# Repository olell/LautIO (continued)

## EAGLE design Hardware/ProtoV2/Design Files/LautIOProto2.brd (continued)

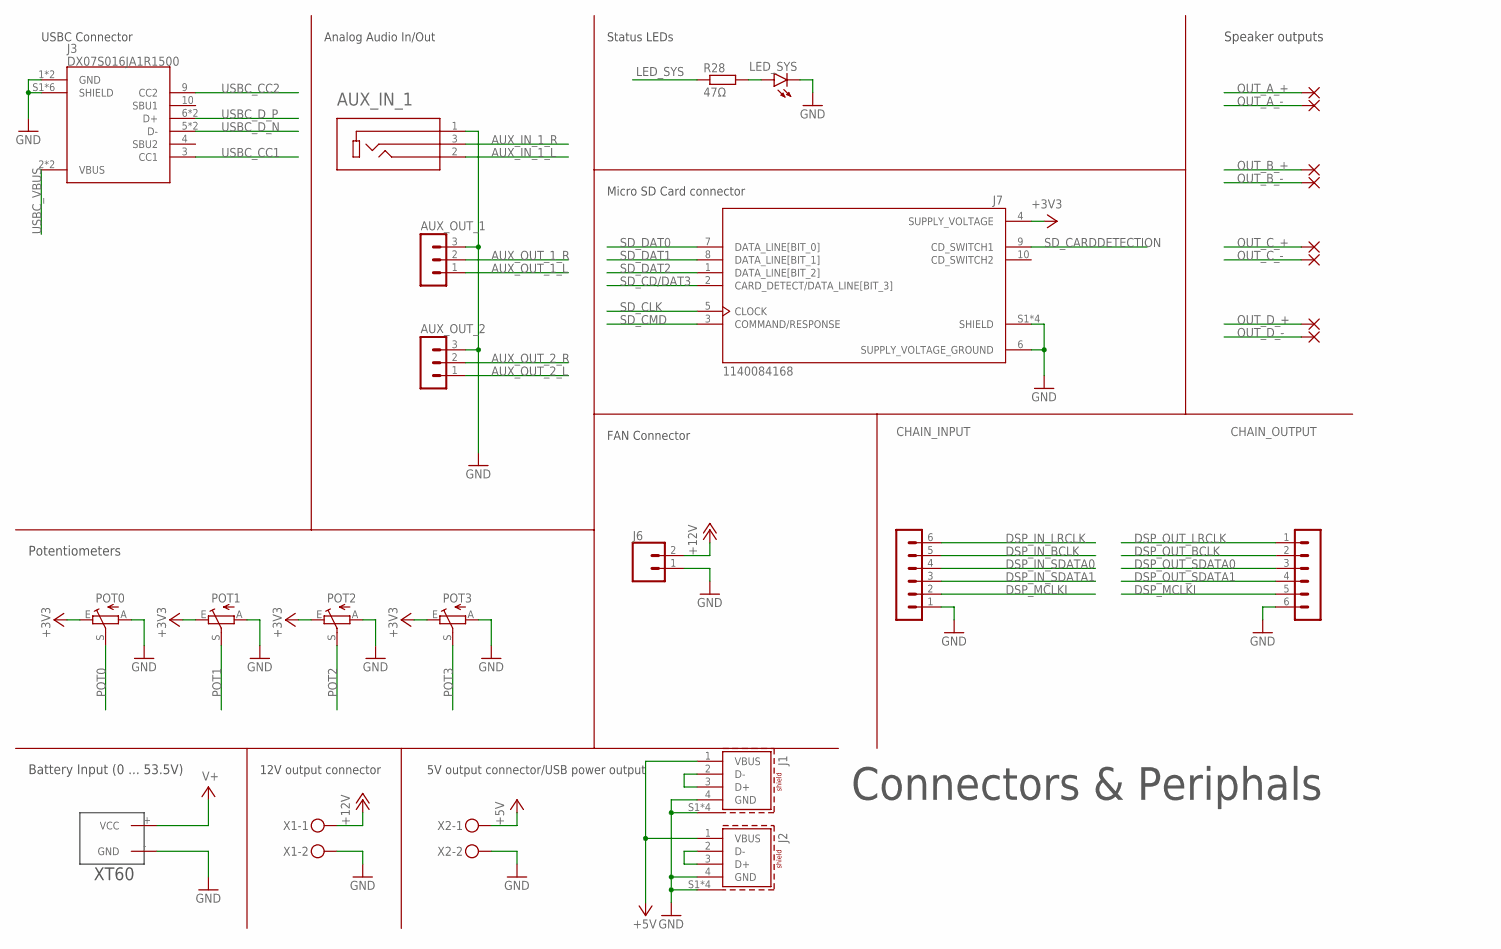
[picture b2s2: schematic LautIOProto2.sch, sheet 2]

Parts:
AUX_IN_1: SJ1-3523N; CUI_SJ1-3523N
AUX_OUT_1, AUX_OUT_2: MA03-1
CHAIN_INPUT: MA06-1
CHAIN_OUTPUT: MA06-1
J1, J2: 614004134726
J3: DX07S016JA1R1500; JAE_DX07S016JA1R1500
J6: CONN_02PTH3; 1X02_LONGPADS
J7: 1140084168; AMPHENOL_1140084168
LED_SYS: LEDSML0603; SML0603
PAD1, PAD2, PAD3, PAD4, PAD5, PAD6, PAD7, PAD8: SMD2; SMD1,27-2,54
POT0, POT1, POT2, POT3: TRIM_EU-CIP20C-6MM; CIP20C-6MM
R28: 47Ω; R0603
U$1: XT60
X1, X2: MKDSN1,5/2-5,08

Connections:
+3V3: J7.4 (SUPPLY_VOLTAGE), POT0.E, POT1.E, POT2.E, POT3.E; also elsewhere on the board
+5V: J1.1 (VBUS), J2.1 (VBUS), X2.1; also elsewhere on the board
+12V: J6.2, X1.1; also elsewhere on the board
AUX_IN_1_L: AUX_IN_1.2; also elsewhere on the board
AUX_IN_1_R: AUX_IN_1.3; also elsewhere on the board
AUX_OUT_1_L: AUX_OUT_1.1; also elsewhere on the board
AUX_OUT_1_R: AUX_OUT_1.2; also elsewhere on the board
AUX_OUT_2_L: AUX_OUT_2.1; also elsewhere on the board
AUX_OUT_2_R: AUX_OUT_2.2; also elsewhere on the board
DSP_IN_BCLK: CHAIN_INPUT.5; also elsewhere on the board
DSP_IN_LRCLK: CHAIN_INPUT.6; also elsewhere on the board
DSP_IN_SDATA0: CHAIN_INPUT.4; also elsewhere on the board
DSP_IN_SDATA1: CHAIN_INPUT.3; also elsewhere on the board
DSP_MCLKI: CHAIN_INPUT.2, CHAIN_OUTPUT.5; also elsewhere on the board
DSP_OUT_BCLK: CHAIN_OUTPUT.2; also elsewhere on the board
DSP_OUT_LRCLK: CHAIN_OUTPUT.1; also elsewhere on the board
DSP_OUT_SDATA0: CHAIN_OUTPUT.3; also elsewhere on the board
DSP_OUT_SDATA1: CHAIN_OUTPUT.4; also elsewhere on the board
GND: AUX_IN_1.1, AUX_OUT_1.3, AUX_OUT_2.3, CHAIN_INPUT.1, CHAIN_OUTPUT.6, J1.4 (GND), J1.S1 (SHIELD), J1.S2 (SHIELD), J1.S3 (SHIELD), J1.S4 (SHIELD), J2.4 (GND), J2.S1 (SHIELD), J2.S2 (SHIELD), J2.S3 (SHIELD), J2.S4 (SHIELD), J3.1 (GND), J3.12 (GND), J3.S1 (SHIELD), J3.S2 (SHIELD), J3.S3 (SHIELD), J3.S4 (SHIELD), J3.S5 (SHIELD), J3.S6 (SHIELD), J6.1, J7.6 (SUPPLY_VOLTAGE_GROUND), J7.S1 (SHIELD), J7.S2 (SHIELD), J7.S3 (SHIELD), J7.S4 (SHIELD), LED_SYS.C, POT0.A, POT1.A, POT2.A, POT3.A, U$1.- (GND), X1.2, X2.2; also elsewhere on the board
LED_SYS: R28.1; also elsewhere on the board
unnamed: J2.2 (D-), J2.3 (D+)
unnamed: J1.2 (D-), J1.3 (D+)
unnamed: LED_SYS.A, R28.2
OUT_A_+: PAD1.1; also elsewhere on the board
OUT_A_-: PAD2.1; also elsewhere on the board
OUT_B_+: PAD4.1; also elsewhere on the board
OUT_B_-: PAD3.1; also elsewhere on the board
OUT_C_+: PAD5.1; also elsewhere on the board
OUT_C_-: PAD6.1; also elsewhere on the board
OUT_D_+: PAD8.1; also elsewhere on the board
OUT_D_-: PAD7.1; also elsewhere on the board
POT0: POT0.S; also elsewhere on the board
POT1: POT1.S; also elsewhere on the board
POT2: POT2.S; also elsewhere on the board
POT3: POT3.S; also elsewhere on the board
SD_CARDDETECTION: J7.9 (CD_SWITCH1); also elsewhere on the board
SD_CD/DAT3: J7.2 (CARD_DETECT/DATA_LINE[BIT_3]); also elsewhere on the board
SD_CLK: J7.5 (CLOCK); also elsewhere on the board
SD_CMD: J7.3 (COMMAND/RESPONSE); also elsewhere on the board
SD_DAT0: J7.7 (DATA_LINE[BIT_0]); also elsewhere on the board
SD_DAT1: J7.8 (DATA_LINE[BIT_1]); also elsewhere on the board
SD_DAT2: J7.1 (DATA_LINE[BIT_2]); also elsewhere on the board
USBC_CC1: J3.3 (CC1); also elsewhere on the board
USBC_CC2: J3.9 (CC2); also elsewhere on the board
USBC_D_N: J3.5 (D-), J3.8 (D-); also elsewhere on the board
USBC_D_P: J3.6 (D+), J3.7 (D+); also elsewhere on the board
USBC_VBUS: J3.2 (VBUS), J3.11 (VBUS); also elsewhere on the board
V+: U$1.+ (VCC); also elsewhere on the board

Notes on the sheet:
Battery Input (0 ... 53.5V)
12V output connector
Connectors & Periphals
5V output connector/USB power output
Potentiometers
Speaker outputs
USBC Connector
Micro SD Card connector
Analog Audio In/Out
Status LEDs
FAN Connector

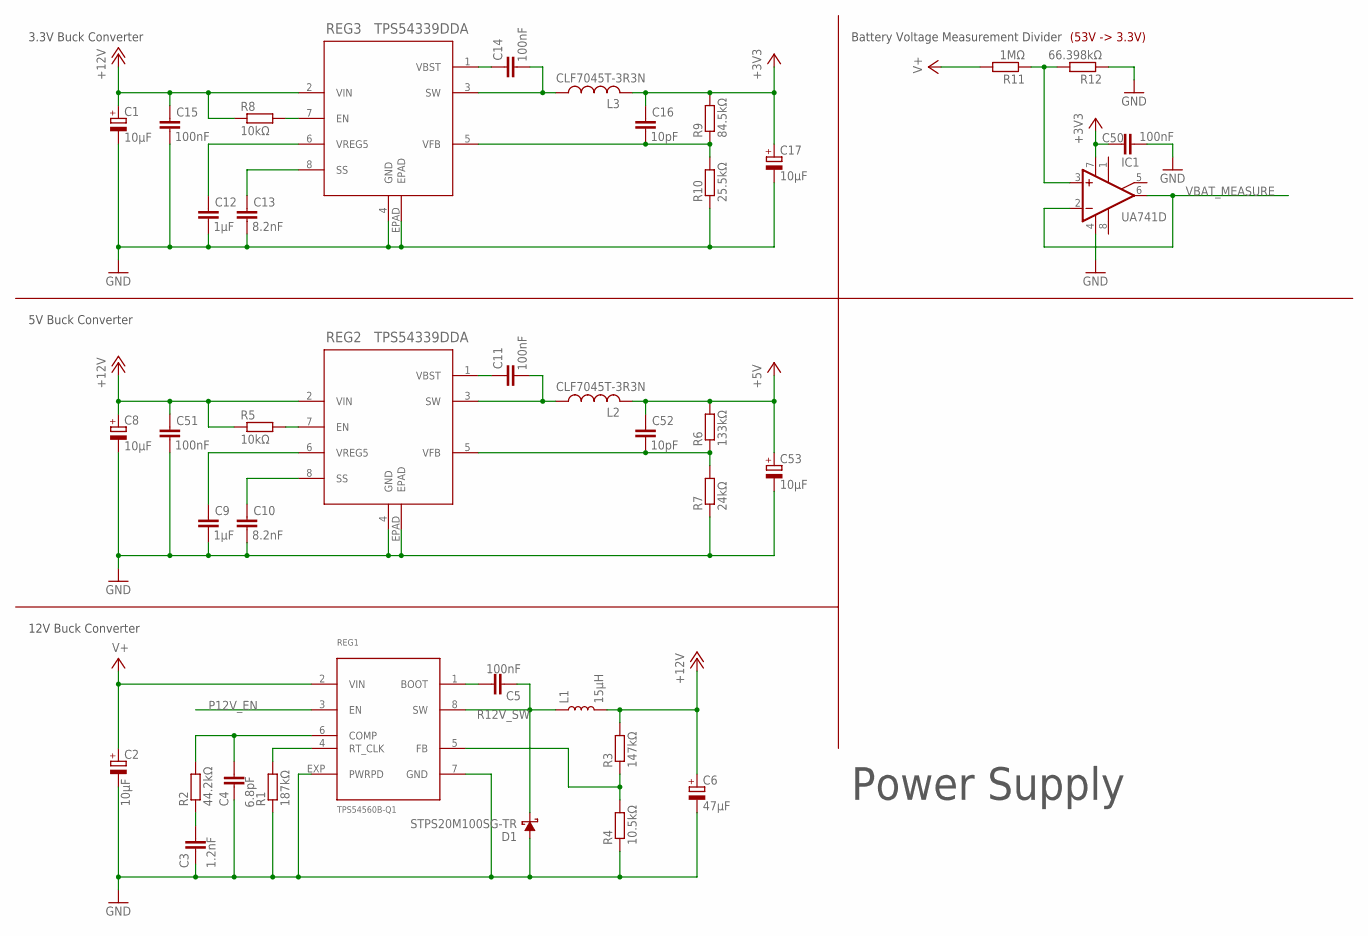
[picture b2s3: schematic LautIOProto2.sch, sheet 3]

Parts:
C1, C2, C8, C17, C53: 10µF; 153CLV-0605
C3: 1.2nF; C0603
C4: 6.8pF; C0603
C5, C11, C14, C15, C50, C51: 100nF; C0603
C6: 47µF; 153CLV-0807
C9, C12: 1µF; C3216
C10, C13: 8.2nF; C0603
C16, C52: 10pF; C0603
D1: STPS20M100SG-TR; TO-263/D2PAK
IC1: UA741D; SO08
L1: 15µH; INDUCTOR_SDR1307
L2, L3: CLF7045T-3R3N; L5650M
R1: 187kΩ; R0603
R2: 44.2kΩ; R0603
R3: 147kΩ; R0603
R4: 10.5kΩ; R0603
R5, R8: 10kΩ; R0603
R6: 133kΩ; R0603
R7: 24kΩ; R0603
R9: 84.5kΩ; R0603
R10: 25.5kΩ; R0603
R11: 1MΩ; R0603
R12: 66.398kΩ; R0603
REG1: TPS54560B-Q1; HSOP8
REG2, REG3: TPS54339DDA; DDA8_3P1X2P4_TEX

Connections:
+3V3: C16.1, C17.+, C50.1, IC1.7 (V+), L3.2, R9.2; also elsewhere on the board
+5V: C52.1, C53.+, L2.2, R6.2; also elsewhere on the board
+12V: C1.+, C6.+, C8.+, C15.1, C51.1, L1.P$2 (2), R3.2, R5.1, R8.1, REG2.2 (VIN), REG3.2 (VIN); also elsewhere on the board
GND: C1.-, C2.-, C3.2, C4.2, C6.-, C8.-, C9.2, C10.2, C12.2, C13.2, C15.2, C17.-, C50.2, C51.2, C53.-, D1.1 (A), D1.3 (A), IC1.4 (V-), R1.1, R4.1, R7.1, R10.1, R12.1, REG1.7 (GND), REG1.EXP (PWRPD), REG2.4 (GND), REG2.EPAD, REG3.4 (GND), REG3.EPAD; also elsewhere on the board
unnamed: R1.2, REG1.4 (RT_CLK)
unnamed: C4.1, R2.2, REG1.6 (COMP)
unnamed: C3.1, R2.1
unnamed: C5.1, REG1.1 (BOOT)
unnamed: R3.1, R4.2, REG1.5 (FB)
unnamed: R5.2, REG2.7 (EN)
unnamed: C10.1, REG2.8 (SS)
unnamed: C9.1, REG2.6 (VREG5)
unnamed: C11.1, REG2.1 (VBST)
unnamed: R8.2, REG3.7 (EN)
unnamed: C14.1, REG3.1 (VBST)
unnamed: C13.1, REG3.8 (SS)
unnamed: C12.1, REG3.6 (VREG5)
unnamed: C14.2, L3.1, REG3.3 (SW)
unnamed: C16.2, R9.1, R10.2, REG3.5 (VFB)
unnamed: IC1.3 (+IN), R11.1, R12.2
unnamed: C11.2, L2.1, REG2.3 (SW)
unnamed: C52.2, R6.1, R7.2, REG2.5 (VFB)
P12V_EN: REG1.3 (EN)
R12V_SW: C5.2, D1.2 (C), L1.P$1 (1), REG1.8 (SW)
V+: C2.+, R11.2, REG1.2 (VIN); also elsewhere on the board
VBAT_MEASURE: IC1.2 (-IN), IC1.6 (OUT); also elsewhere on the board

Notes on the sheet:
Power Supply
12V Buck Converter
5V Buck Converter
3.3V Buck Converter
Battery Voltage Measurement Divider
(53V -> 3.3V)

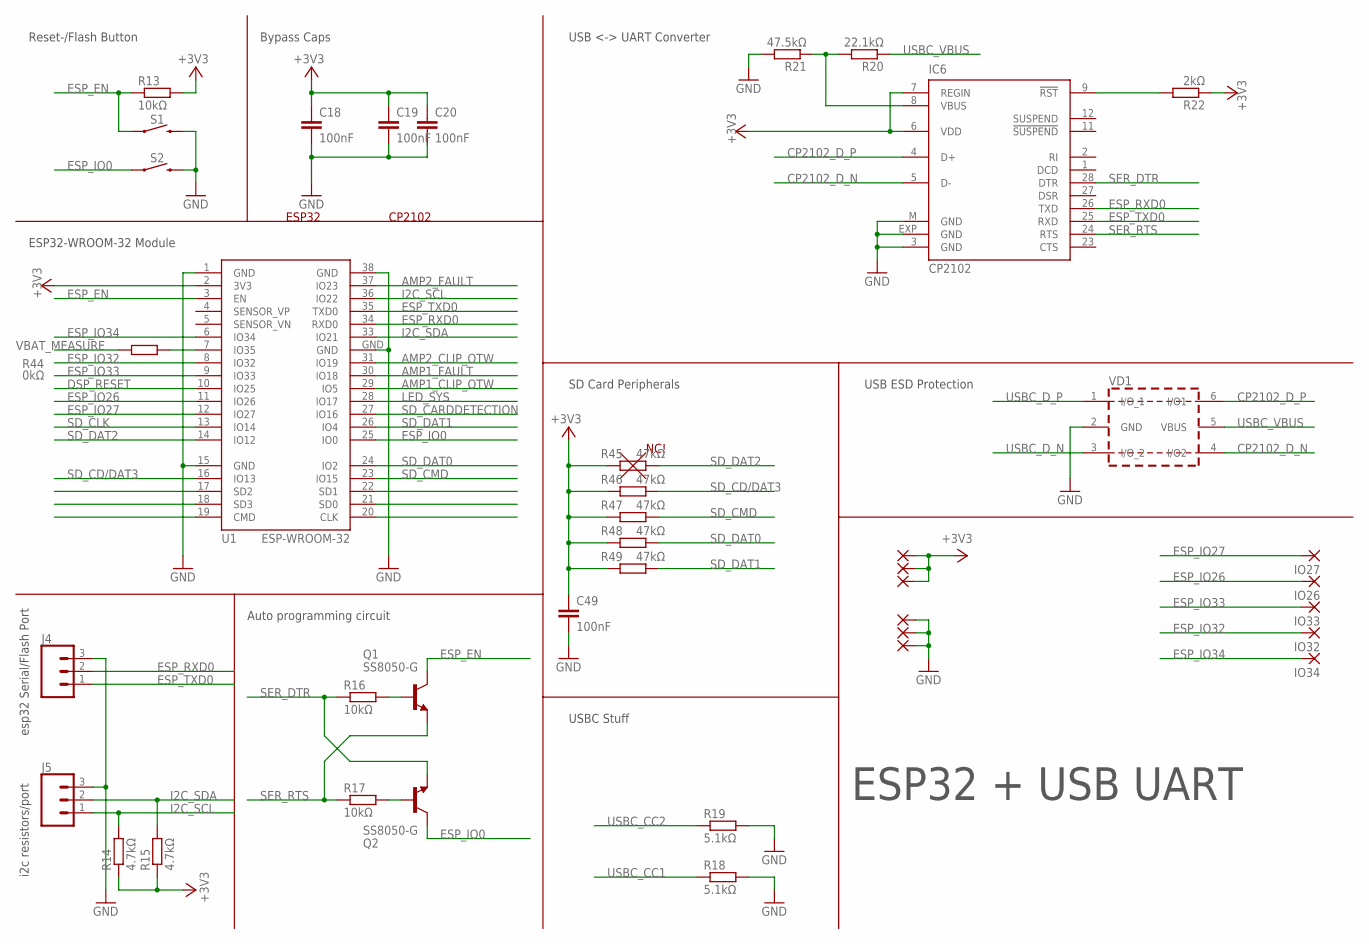
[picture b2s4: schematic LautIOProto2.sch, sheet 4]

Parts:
3V3IO: SMD2; SMD1,27-2,54
C18, C19, C20, C49: 100nF; C0603
IC6: CP2102; MLP28
IO1, IO2, IO3, IO4, IO5, IO26, IO27, IO32, IO33, IO34: SMD2; SMD1,27-2,54
J4, J5: 455-1750-1-ND; 1X03
Q1, Q2: SS8050-G; SOT23-BEC
R13, R16, R17: 10kΩ; R0603
R14, R15: 4.7kΩ; R0603
R18, R19: 5.1kΩ; R0603
R20: 22.1kΩ; R0603
R21: 47.5kΩ; R0603
R22: 2kΩ; R0603
R44: 0kΩ; R0603
R45, R46, R47, R48, R49: 47kΩ; R0603
S1, S2: MOMENTARY-SWITCH-SPST-SMD-6.2MM-TALL; TACTILE_SWITCH_SMD_6.2MM_TALL
U1: ESP-WROOM-32
VD1: USBLC6-2SC6; SOT-23-6L

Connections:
+3V3: 3V3IO.1, C18.1, C19.1, C20.1, C49.1, IC6.6 (VDD), IC6.7 (REGIN), IO2.1, IO3.1, R13.2, R14.1, R15.1, R22.1, R45.1, R46.1, R47.1, R48.1, R49.1, U1.2 (3V3); also elsewhere on the board
AMP1_CLIP_OTW: U1.29 (IO5); also elsewhere on the board
AMP1_FAULT: U1.30 (IO18); also elsewhere on the board
AMP2_CLIP_OTW: U1.31 (IO19); also elsewhere on the board
AMP2_FAULT: U1.37 (IO23); also elsewhere on the board
CP2102_D_N: IC6.5 (D-), VD1.4 (I/O2)
CP2102_D_P: IC6.4 (D+), VD1.6 (I/O1)
DSP_RESET: U1.10 (IO25); also elsewhere on the board
ESP_EN: Q1.C, R13.1, S1.A2 (1), U1.3 (EN)
ESP_IO0: Q2.C, S2.A2 (1), U1.25 (IO0)
ESP_IO26: IO26.1, U1.11 (IO26)
ESP_IO27: IO27.1, U1.12 (IO27)
ESP_IO32: IO32.1, U1.8 (IO32)
ESP_IO33: IO33.1, U1.9 (IO33)
ESP_IO34: IO34.1, U1.6 (IO34)
ESP_RXD0: IC6.26 (TXD), J4.2, U1.34 (RXD0)
ESP_TXD0: IC6.25 (RXD), J4.1, U1.35 (TXD0)
GND: C18.2, C19.2, C20.2, C49.2, IC6.3 (GND), IC6.EXP (GND), IC6.M (GND), IO1.1, IO4.1, IO5.1, J4.3, J5.3, R18.2, R19.2, R21.2, S1.B2 (2), S2.B2 (2), U1.1 (GND), U1.15 (GND), U1.38 (GND), U1.GND, VD1.2 (GND); also elsewhere on the board
I2C_SCL: J5.1, R14.2, U1.36 (IO22); also elsewhere on the board
I2C_SDA: J5.2, R15.2, U1.33 (IO21); also elsewhere on the board
LED_SYS: U1.28 (IO17); also elsewhere on the board
unnamed: Q1.B, R16.2
unnamed: R44.2, U1.7 (IO35)
unnamed: Q2.B, R17.2
unnamed: IC6.8 (VBUS), R20.2, R21.1
unnamed: IC6.9 (!RST), R22.2
SD_CARDDETECTION: U1.27 (IO16); also elsewhere on the board
SD_CD/DAT3: R46.2, U1.16 (IO13); also elsewhere on the board
SD_CLK: U1.13 (IO14); also elsewhere on the board
SD_CMD: R47.2, U1.23 (IO15); also elsewhere on the board
SD_DAT0: R48.2, U1.24 (IO2); also elsewhere on the board
SD_DAT1: R49.2, U1.26 (IO4); also elsewhere on the board
SD_DAT2: R45.2, U1.14 (IO12); also elsewhere on the board
SER_DTR: IC6.28 (DTR), Q2.E, R16.1
SER_RTS: IC6.24 (RTS), Q1.E, R17.1
USBC_CC1: R18.1; also elsewhere on the board
USBC_CC2: R19.1; also elsewhere on the board
USBC_D_N: VD1.3 (I/O_2); also elsewhere on the board
USBC_D_P: VD1.1 (I/O_1); also elsewhere on the board
USBC_VBUS: R20.1, VD1.5 (VBUS); also elsewhere on the board
VBAT_MEASURE: R44.1; also elsewhere on the board

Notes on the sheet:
ESP32 + USB UART
Reset-/Flash Button
Bypass Caps
ESP32-WROOM-32 Module
esp32 Serial/Flash Port
i2c resistors/port
Auto programming circuit
USBC Stuff
ESP32
CP2102
USB <-> UART Converter
USB ESD Protection
NC!
SD Card Peripherals

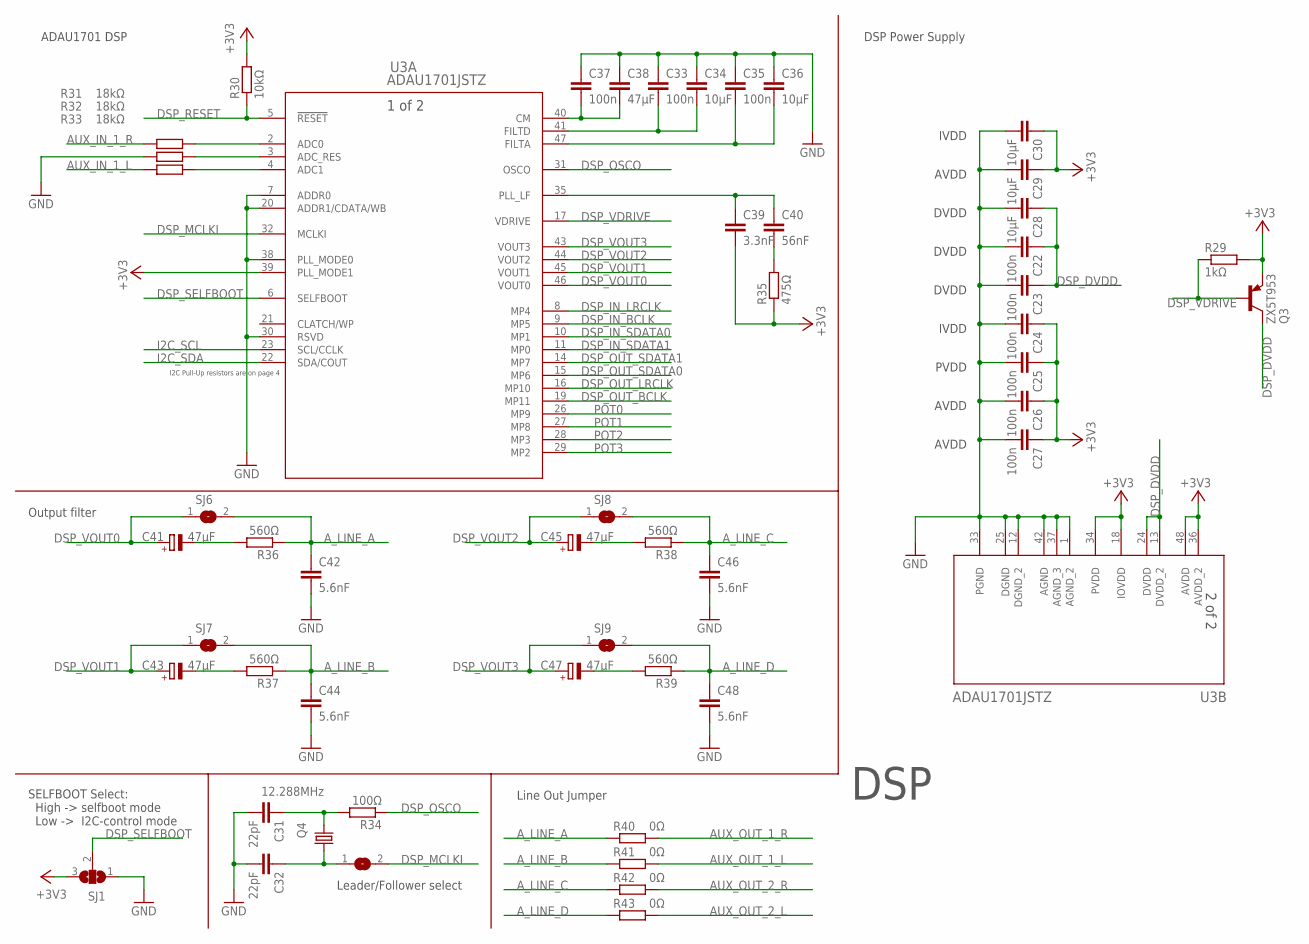
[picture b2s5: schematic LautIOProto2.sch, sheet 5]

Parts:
C22, C23, C24, C25, C26, C27, C33, C35, C37: 100n; C0603
C28, C29, C30, C34, C36: 10µF; C1206K
C31, C32: 22pF; C0603
C38: 47µF; C1206K
C39: 3.3nF; C0603
C40: 56nF; C0603
C41, C43, C45, C47: 47µF; 153CLV-0605
C42, C44, C46, C48: 5.6nF; C0603
Q3: ZX5T953; SOT223
Q4: 12.288MHz; CSM-7X-DU
R29: 1kΩ; R0603
R30: 10kΩ; R0603
R31, R32, R33: 18kΩ; R0603
R34: 100Ω; R0603
R35: 475Ω; R0603
R36, R37, R38, R39: 560Ω; R0603
R40, R41, R42, R43: 0Ω; R0603
SJ1: SJ2W; SJ_2
SJ2, SJ6, SJ7, SJ8, SJ9: SJ
U3: ADAU1701JSTZ; ST_48_ADI

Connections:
+3V3: C24.1, C25.1, C26.1, C27.1, C29.1, C30.1, C39.2, Q3.3 (E), R29.2, R30.2, R35.1, SJ1.3, U3.18 (IOVDD), U3.34 (PVDD), U3.36 (AVDD_2), U3.39 (PLL_MODE1), U3.48 (AVDD); also elsewhere on the board
AUX_IN_1_L: R33.2; also elsewhere on the board
AUX_IN_1_R: R31.2; also elsewhere on the board
AUX_OUT_1_L: R41.2; also elsewhere on the board
AUX_OUT_1_R: R40.2; also elsewhere on the board
AUX_OUT_2_L: R43.2; also elsewhere on the board
AUX_OUT_2_R: R42.2; also elsewhere on the board
A_LINE_A: C42.1, R36.1, R40.1, SJ6.2; also elsewhere on the board
A_LINE_B: C44.1, R37.1, R41.1, SJ7.2; also elsewhere on the board
A_LINE_C: C46.1, R38.1, R42.1, SJ8.2; also elsewhere on the board
A_LINE_D: C48.1, R39.1, R43.1, SJ9.2; also elsewhere on the board
CRYSTAL_MCLKI: C32.1, Q4.1, SJ2.1
DSP_DVDD: C22.1, C23.1, C28.1, Q3.2 (C), Q3.4 (C), U3.13 (DVDD_2), U3.24 (DVDD)
DSP_IN_BCLK: U3.9 (MP5); also elsewhere on the board
DSP_IN_LRCLK: U3.8 (MP4); also elsewhere on the board
DSP_IN_SDATA0: U3.10 (MP1); also elsewhere on the board
DSP_IN_SDATA1: U3.11 (MP0); also elsewhere on the board
DSP_MCLKI: SJ2.2, U3.32 (MCLKI); also elsewhere on the board
DSP_OSCO: R34.1, U3.31 (OSCO)
DSP_OUT_BCLK: U3.19 (MP11); also elsewhere on the board
DSP_OUT_LRCLK: U3.16 (MP10); also elsewhere on the board
DSP_OUT_SDATA0: U3.15 (MP6); also elsewhere on the board
DSP_OUT_SDATA1: U3.14 (MP7); also elsewhere on the board
DSP_RESET: R30.1, U3.5 (!RESET); also elsewhere on the board
DSP_SELFBOOT: SJ1.2, U3.6 (SELFBOOT)
DSP_VDRIVE: Q3.1 (B), R29.1, U3.17 (VDRIVE)
DSP_VOUT0: C41.+, SJ6.1, U3.46 (VOUT0)
DSP_VOUT1: C43.+, SJ7.1, U3.45 (VOUT1)
DSP_VOUT2: C45.+, SJ8.1, U3.44 (VOUT2)
DSP_VOUT3: C47.+, SJ9.1, U3.43 (VOUT3)
GND: C22.2, C23.2, C24.2, C25.2, C26.2, C27.2, C28.2, C29.2, C30.2, C31.2, C32.2, C33.1, C34.1, C35.1, C36.1, C37.1, C38.1, C42.2, C44.2, C46.2, C48.2, R32.2, SJ1.1, U3.1 (AGND_2), U3.7 (ADDR0), U3.12 (DGND_2), U3.20 (ADDR1/CDATA/WB), U3.25 (DGND), U3.30 (RSVD), U3.33 (PGND), U3.37 (AGND_3), U3.38 (PLL_MODE0), U3.42 (AGND); also elsewhere on the board
I2C_SCL: U3.23 (SCL/CCLK); also elsewhere on the board
I2C_SDA: U3.22 (SDA/COUT); also elsewhere on the board
unnamed: R31.1, U3.2 (ADC0)
unnamed: R32.1, U3.3 (ADC_RES)
unnamed: R33.1, U3.4 (ADC1)
unnamed: C31.1, Q4.2, R34.2
unnamed: C33.2, C34.2, U3.41 (FILTD)
unnamed: C35.2, C36.2, U3.47 (FILTA)
unnamed: C37.2, C38.2, U3.40 (CM)
unnamed: C39.1, C40.1, U3.35 (PLL_LF)
unnamed: C40.2, R35.2
unnamed: C41.-, R36.2
unnamed: C43.-, R37.2
unnamed: C45.-, R38.2
unnamed: C47.-, R39.2
POT0: U3.26 (MP9); also elsewhere on the board
POT1: U3.27 (MP8); also elsewhere on the board
POT2: U3.28 (MP3); also elsewhere on the board
POT3: U3.29 (MP2); also elsewhere on the board

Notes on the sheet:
DSP
DSP Power Supply
AVDD
PVDD
IVDD
DVDD
I2C Pull-Up resistors are on page 4
SELFBOOT Select: High -> selfboot mode Low -> I2C-control mode
Output filter
Line Out Jumper
ADAU1701 DSP
Leader/Follower select

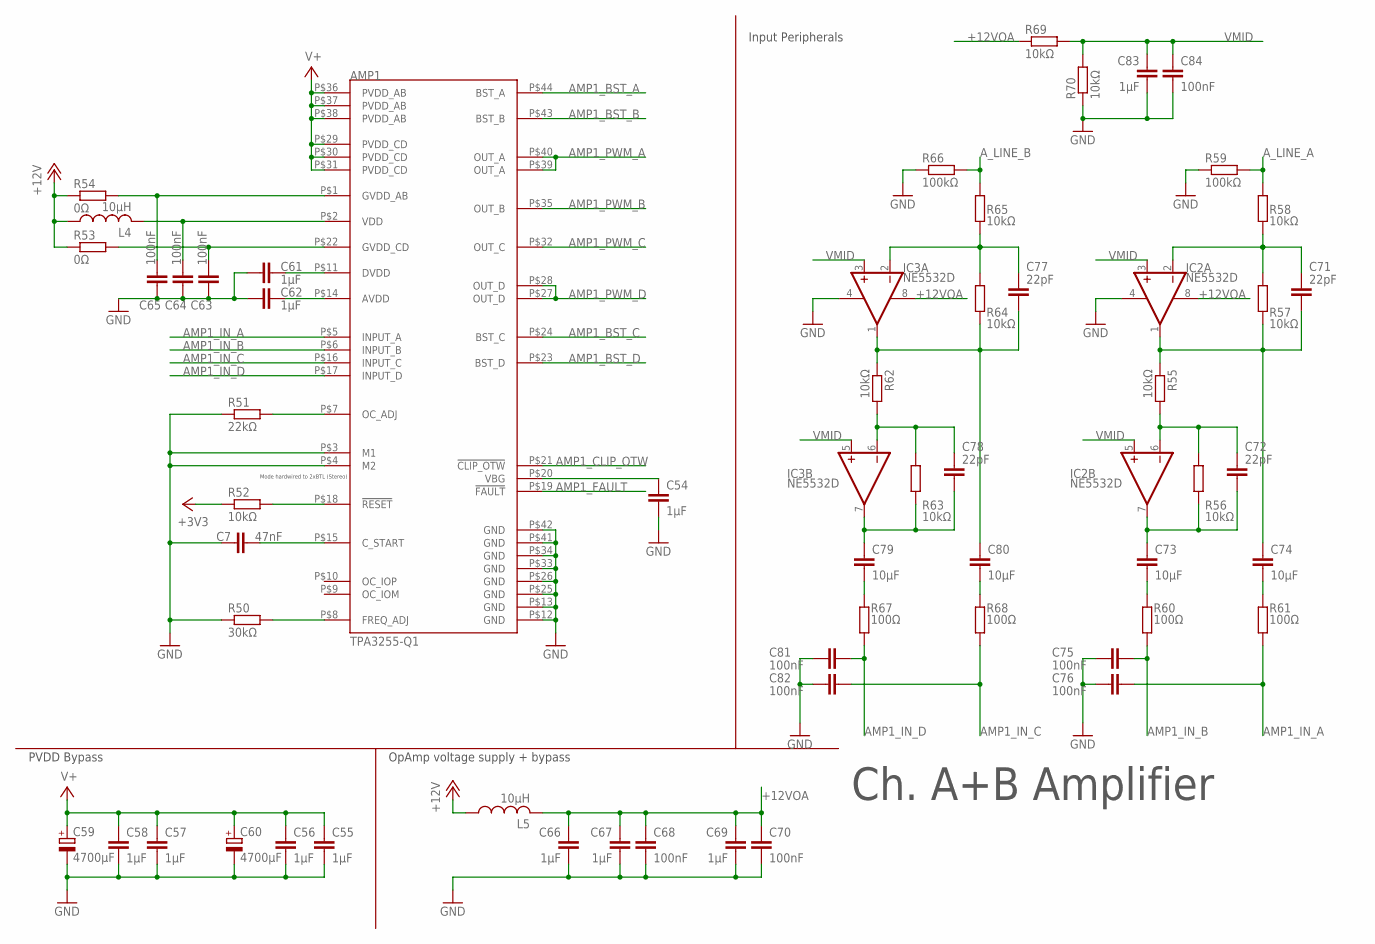
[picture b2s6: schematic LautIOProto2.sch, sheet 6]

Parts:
AMP1: TPA3255-Q1; HTSSOP44
C7: 47nF; C0603
C54, C55, C56, C57, C58, C61, C62, C66, C67, C69, C83: 1µF; C3216
C59, C60: 4700µF; EB22,5D
C63, C64, C65, C68, C70, C75, C76, C81, C82, C84: 100nF; C0603
C71, C72, C77, C78: 22pF; C0603
C73, C74, C79, C80: 10µF; C3216
IC2, IC3: NE5532D; SO08
L4, L5: 10µH; L2012C
R50: 30kΩ; R0603
R51: 22kΩ; R0603
R52, R55, R56, R57, R58, R62, R63, R64, R65, R69, R70: 10kΩ; R0603
R53, R54: 0Ω; R0603
R59, R66: 100kΩ; R0603
R60, R61, R67, R68: 100Ω; R0603

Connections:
+3V3: R52.1; also elsewhere on the board
+12V: L4.1, L5.1, R53.1, R54.1; also elsewhere on the board
+12VOA: C66.1, C67.1, C68.1, C69.1, C70.1, IC2.8 (V+), IC3.8 (V+), L5.2, R69.1
AMP1_BST_A: AMP1.P$44 (BST_A); also elsewhere on the board
AMP1_BST_B: AMP1.P$43 (BST_B); also elsewhere on the board
AMP1_BST_C: AMP1.P$24 (BST_C); also elsewhere on the board
AMP1_BST_D: AMP1.P$23 (BST_D); also elsewhere on the board
AMP1_CLIP_OTW: AMP1.P$21 (!CLIP_OTW); also elsewhere on the board
AMP1_FAULT: AMP1.P$19 (!FAULT); also elsewhere on the board
AMP1_IN_A: AMP1.P$5 (INPUT_A), C76.2, R61.2
AMP1_IN_B: AMP1.P$6 (INPUT_B), C75.2, R60.2
AMP1_IN_C: AMP1.P$16 (INPUT_C), C82.2, R68.2
AMP1_IN_D: AMP1.P$17 (INPUT_D), C81.2, R67.2
AMP1_PWM_A: AMP1.P$39 (OUT_A), AMP1.P$40 (OUT_A); also elsewhere on the board
AMP1_PWM_B: AMP1.P$35 (OUT_B); also elsewhere on the board
AMP1_PWM_C: AMP1.P$32 (OUT_C); also elsewhere on the board
AMP1_PWM_D: AMP1.P$27 (OUT_D), AMP1.P$28 (OUT_D); also elsewhere on the board
A_LINE_A: R58.1, R59.2; also elsewhere on the board
A_LINE_B: R65.1, R66.2; also elsewhere on the board
GND: AMP1.P$3 (M1), AMP1.P$4 (M2), AMP1.P$12 (GND), AMP1.P$13 (GND), AMP1.P$25 (GND), AMP1.P$26 (GND), AMP1.P$33 (GND), AMP1.P$34 (GND), AMP1.P$41 (GND), AMP1.P$42 (GND), C7.1, C54.2, C55.2, C56.2, C57.2, C58.2, C59.-, C60.-, C61.2, C62.2, C63.2, C64.2, C65.2, C66.2, C67.2, C68.2, C69.2, C70.2, C75.1, C76.1, C81.1, C82.1, C83.2, C84.2, IC2.4 (V-), IC3.4 (V-), R50.1, R51.1, R59.1, R66.1, R70.1; also elsewhere on the board
unnamed: AMP1.P$15 (C_START), C7.2
unnamed: AMP1.P$8 (FREQ_ADJ), R50.2
unnamed: AMP1.P$7 (OC_ADJ), R51.2
unnamed: AMP1.P$18 (!RESET), R52.2
unnamed: AMP1.P$20 (VBG), C54.1
unnamed: AMP1.P$11 (DVDD), C61.1
unnamed: AMP1.P$14 (AVDD), C62.1
unnamed: AMP1.P$1 (GVDD_AB), C65.1, R54.2
unnamed: AMP1.P$2 (VDD), C64.1, L4.2
unnamed: AMP1.P$22 (GVDD_CD), C63.1, R53.2
unnamed: C71.1, IC2.2 (-IN), R57.1, R58.2
unnamed: C71.2, C74.1, IC2.1 (OUT), R55.1, R57.2
unnamed: C72.1, IC2.6 (-IN), R55.2, R56.1
unnamed: C77.1, IC3.2 (-IN), R64.1, R65.2
unnamed: C72.2, C73.1, IC2.7 (OUT), R56.2
unnamed: C77.2, C80.1, IC3.1 (OUT), R62.1, R64.2
unnamed: C78.1, IC3.6 (-IN), R62.2, R63.1
unnamed: C74.2, R61.1
unnamed: C73.2, R60.1
unnamed: C78.2, C79.1, IC3.7 (OUT), R63.2
unnamed: C80.2, R68.1
unnamed: C79.2, R67.1
V+: AMP1.P$29 (PVDD_CD), AMP1.P$30 (PVDD_CD), AMP1.P$31 (PVDD_CD), AMP1.P$36 (PVDD_AB), AMP1.P$37 (PVDD_AB), AMP1.P$38 (PVDD_AB), C55.1, C56.1, C57.1, C58.1, C59.+, C60.+; also elsewhere on the board
VMID: C83.1, C84.1, IC2.3 (+IN), IC2.5 (+IN), IC3.3 (+IN), IC3.5 (+IN), R69.2, R70.2

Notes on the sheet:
Ch. A+B Amplifier
PVDD Bypass
Mode hardwired to 2xBTL (Stereo)
OpAmp voltage supply + bypass
Input Peripherals

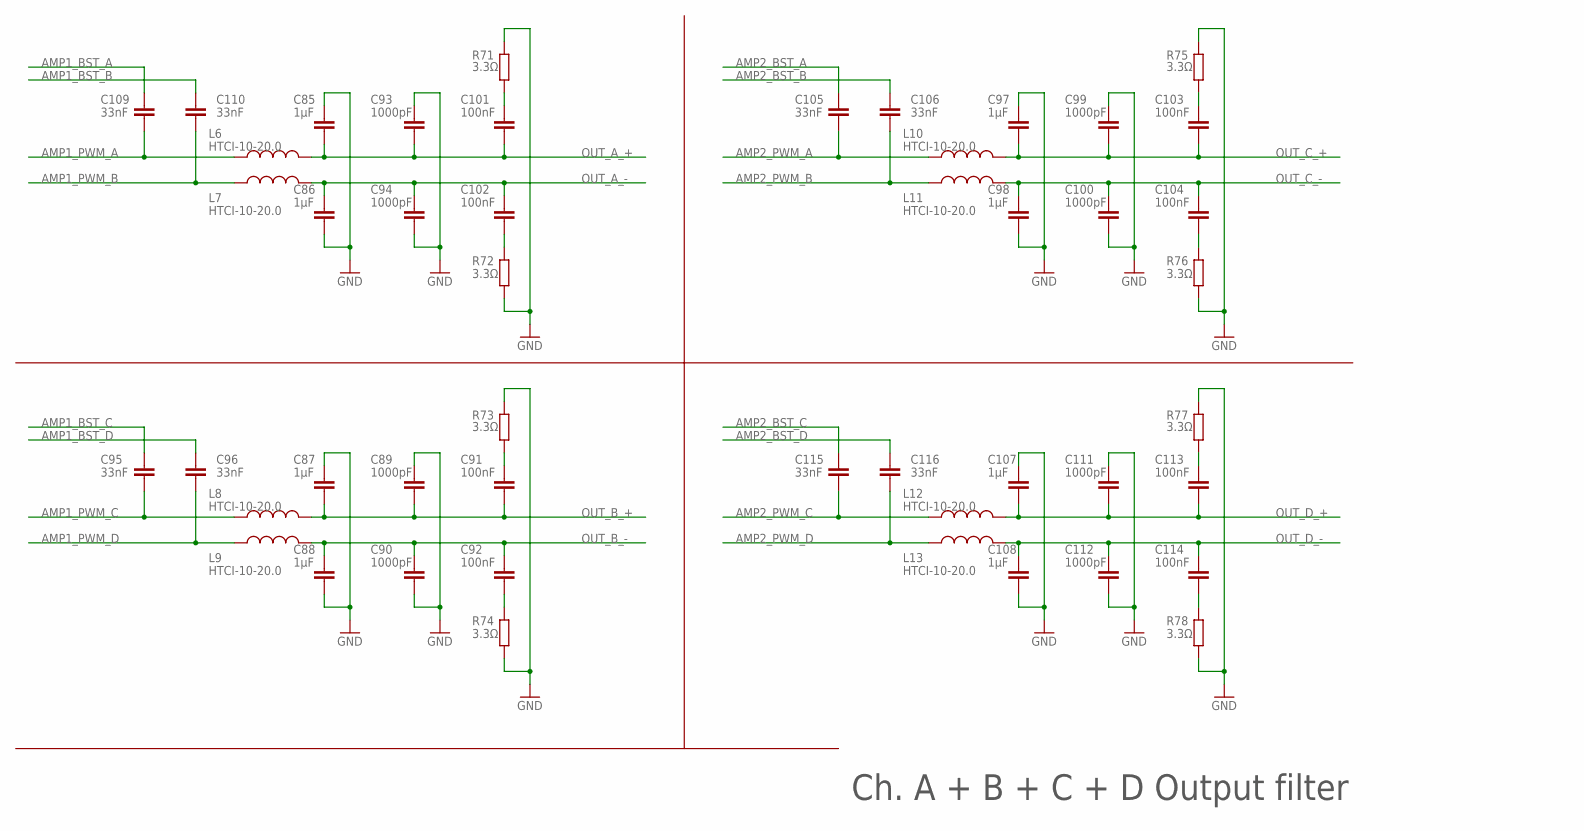
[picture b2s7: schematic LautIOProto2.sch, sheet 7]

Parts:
C85, C86, C87, C88, C97, C98, C107, C108: 1µF; C150-091X182
C89, C90, C93, C94, C99, C100, C111, C112: 1000pF; C0805
C91, C92, C101, C102, C103, C104, C113, C114: 100nF; C0805
C95, C96, C105, C106, C109, C110, C115, C116: 33nF; C0603
L6, L7, L8, L9, L10, L11, L12, L13: HTCI-10-20.0; HCTI-10-20.0
R71, R72, R73, R74, R75, R76, R77, R78: 3.3Ω; R0603

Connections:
AMP1_BST_A: C109.1; also elsewhere on the board
AMP1_BST_B: C110.1; also elsewhere on the board
AMP1_BST_C: C95.1; also elsewhere on the board
AMP1_BST_D: C96.1; also elsewhere on the board
AMP1_PWM_A: C109.2, L6.P$1 (1); also elsewhere on the board
AMP1_PWM_B: C110.2, L7.P$1 (1); also elsewhere on the board
AMP1_PWM_C: C95.2, L8.P$1 (1); also elsewhere on the board
AMP1_PWM_D: C96.2, L9.P$1 (1); also elsewhere on the board
AMP2_BST_A: C105.1; also elsewhere on the board
AMP2_BST_B: C106.1; also elsewhere on the board
AMP2_BST_C: C115.1; also elsewhere on the board
AMP2_BST_D: C116.1; also elsewhere on the board
AMP2_PWM_A: C105.2, L10.P$1 (1); also elsewhere on the board
AMP2_PWM_B: C106.2, L11.P$1 (1); also elsewhere on the board
AMP2_PWM_C: C115.2, L12.P$1 (1); also elsewhere on the board
AMP2_PWM_D: C116.2, L13.P$1 (1); also elsewhere on the board
GND: C85.2, C86.2, C87.2, C88.2, C89.2, C90.2, C93.2, C94.2, C97.2, C98.2, C99.2, C100.2, C107.2, C108.2, C111.2, C112.2, R71.2, R72.2, R73.2, R74.2, R75.2, R76.2, R77.2, R78.2; also elsewhere on the board
unnamed: C92.2, R74.1
unnamed: C102.2, R72.1
unnamed: C101.2, R71.1
unnamed: C91.2, R73.1
unnamed: C104.2, R76.1
unnamed: C103.2, R75.1
unnamed: C114.2, R78.1
unnamed: C113.2, R77.1
OUT_A_+: C85.1, C93.1, C101.1, L6.P$2 (2); also elsewhere on the board
OUT_A_-: C86.1, C94.1, C102.1, L7.P$2 (2); also elsewhere on the board
OUT_B_+: C87.1, C89.1, C91.1, L8.P$2 (2); also elsewhere on the board
OUT_B_-: C88.1, C90.1, C92.1, L9.P$2 (2); also elsewhere on the board
OUT_C_+: C97.1, C99.1, C103.1, L10.P$2 (2); also elsewhere on the board
OUT_C_-: C98.1, C100.1, C104.1, L11.P$2 (2); also elsewhere on the board
OUT_D_+: C107.1, C111.1, C113.1, L12.P$2 (2); also elsewhere on the board
OUT_D_-: C108.1, C112.1, C114.1, L13.P$2 (2); also elsewhere on the board

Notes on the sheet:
Ch. A + B + C + D Output filter

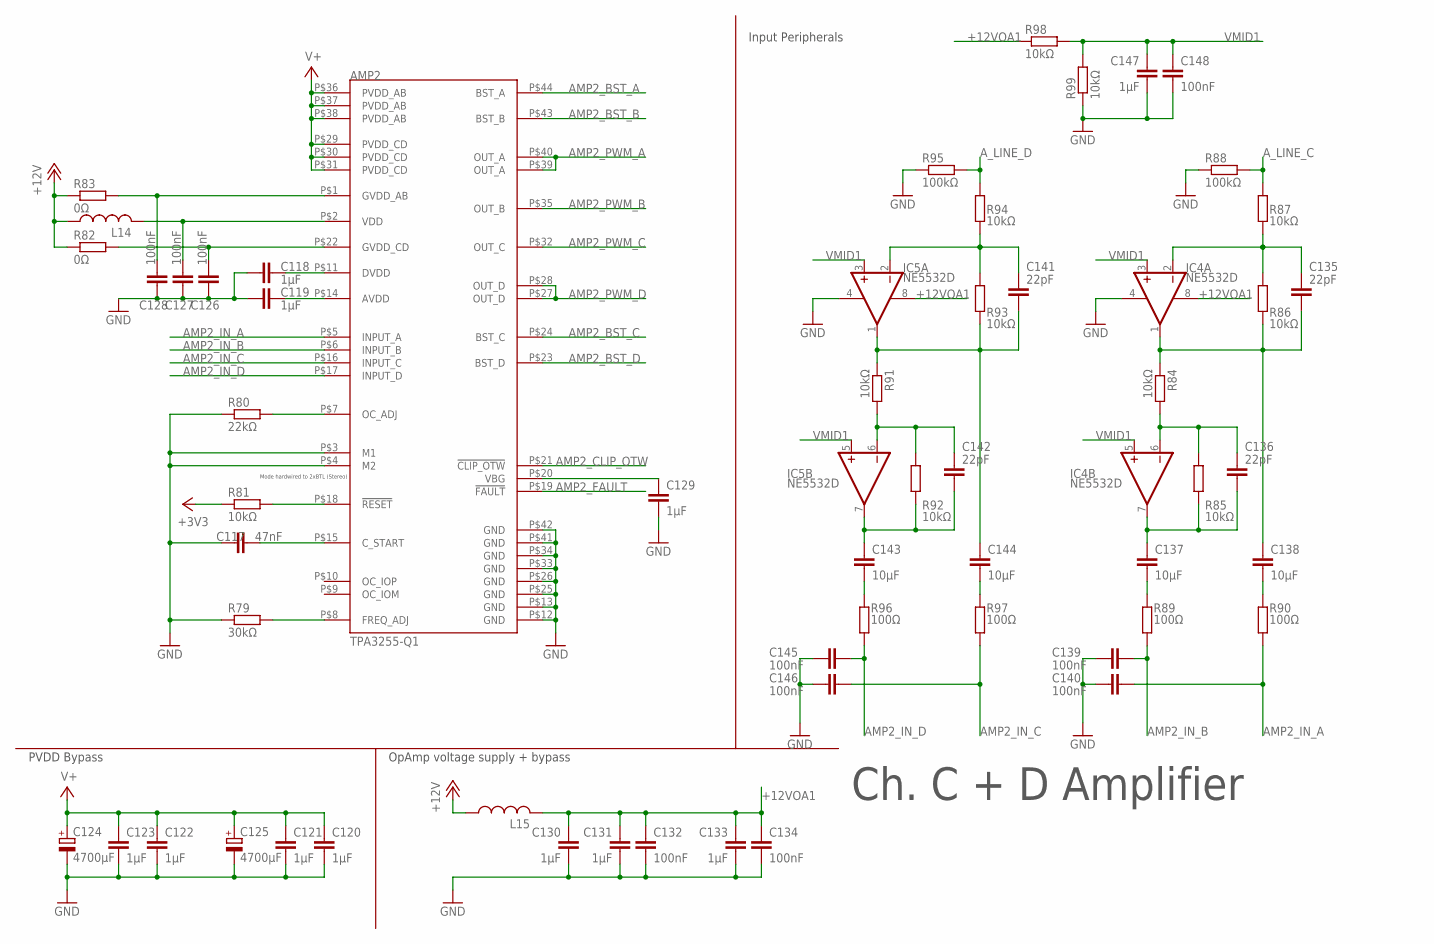
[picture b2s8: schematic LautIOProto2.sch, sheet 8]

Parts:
AMP2: TPA3255-Q1; HTSSOP44
C117: 47nF; C0603
C118, C119, C120, C121, C122, C123, C129, C130, C131, C133, C147: 1µF; C3216
C124, C125: 4700µF; EB22,5D
C126, C127, C128, C132, C134, C139, C140, C145, C146, C148: 100nF; C0603
C135, C136, C141, C142: 22pF; C0603
C137, C138, C143, C144: 10µF; C3216
IC4, IC5: NE5532D; SO08
L14, L15: L-USL2012C; L2012C
R79: 30kΩ; R0603
R80: 22kΩ; R0603
R81, R84, R85, R86, R87, R91, R92, R93, R94, R98, R99: 10kΩ; R0603
R82, R83: 0Ω; R0603
R88, R95: 100kΩ; R0603
R89, R90, R96, R97: 100Ω; R0603

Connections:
+3V3: R81.1; also elsewhere on the board
+12V: L14.1, L15.1, R82.1, R83.1; also elsewhere on the board
+12VOA1: C130.1, C131.1, C132.1, C133.1, C134.1, IC4.8 (V+), IC5.8 (V+), L15.2, R98.1
AMP2_BST_A: AMP2.P$44 (BST_A); also elsewhere on the board
AMP2_BST_B: AMP2.P$43 (BST_B); also elsewhere on the board
AMP2_BST_C: AMP2.P$24 (BST_C); also elsewhere on the board
AMP2_BST_D: AMP2.P$23 (BST_D); also elsewhere on the board
AMP2_CLIP_OTW: AMP2.P$21 (!CLIP_OTW); also elsewhere on the board
AMP2_FAULT: AMP2.P$19 (!FAULT); also elsewhere on the board
AMP2_IN_A: AMP2.P$5 (INPUT_A), C140.2, R90.2
AMP2_IN_B: AMP2.P$6 (INPUT_B), C139.2, R89.2
AMP2_IN_C: AMP2.P$16 (INPUT_C), C146.2, R97.2
AMP2_IN_D: AMP2.P$17 (INPUT_D), C145.2, R96.2
AMP2_PWM_A: AMP2.P$39 (OUT_A), AMP2.P$40 (OUT_A); also elsewhere on the board
AMP2_PWM_B: AMP2.P$35 (OUT_B); also elsewhere on the board
AMP2_PWM_C: AMP2.P$32 (OUT_C); also elsewhere on the board
AMP2_PWM_D: AMP2.P$27 (OUT_D), AMP2.P$28 (OUT_D); also elsewhere on the board
A_LINE_C: R87.1, R88.2; also elsewhere on the board
A_LINE_D: R94.1, R95.2; also elsewhere on the board
GND: AMP2.P$3 (M1), AMP2.P$4 (M2), AMP2.P$12 (GND), AMP2.P$13 (GND), AMP2.P$25 (GND), AMP2.P$26 (GND), AMP2.P$33 (GND), AMP2.P$34 (GND), AMP2.P$41 (GND), AMP2.P$42 (GND), C117.1, C118.2, C119.2, C120.2, C121.2, C122.2, C123.2, C124.-, C125.-, C126.2, C127.2, C128.2, C129.2, C130.2, C131.2, C132.2, C133.2, C134.2, C139.1, C140.1, C145.1, C146.1, C147.2, C148.2, IC4.4 (V-), IC5.4 (V-), R79.1, R80.1, R88.1, R95.1, R99.1; also elsewhere on the board
unnamed: AMP2.P$8 (FREQ_ADJ), R79.2
unnamed: AMP2.P$15 (C_START), C117.2
unnamed: AMP2.P$7 (OC_ADJ), R80.2
unnamed: AMP2.P$18 (!RESET), R81.2
unnamed: AMP2.P$20 (VBG), C129.1
unnamed: AMP2.P$11 (DVDD), C118.1
unnamed: AMP2.P$14 (AVDD), C119.1
unnamed: AMP2.P$1 (GVDD_AB), C128.1, R83.2
unnamed: AMP2.P$2 (VDD), C127.1, L14.2
unnamed: AMP2.P$22 (GVDD_CD), C126.1, R82.2
unnamed: C135.1, IC4.2 (-IN), R86.1, R87.2
unnamed: C135.2, C138.1, IC4.1 (OUT), R84.1, R86.2
unnamed: C136.1, IC4.6 (-IN), R84.2, R85.1
unnamed: C136.2, C137.1, IC4.7 (OUT), R85.2
unnamed: C138.2, R90.1
unnamed: C137.2, R89.1
unnamed: C141.1, IC5.2 (-IN), R93.1, R94.2
unnamed: C141.2, C144.1, IC5.1 (OUT), R91.1, R93.2
unnamed: C142.1, IC5.6 (-IN), R91.2, R92.1
unnamed: C142.2, C143.1, IC5.7 (OUT), R92.2
unnamed: C144.2, R97.1
unnamed: C143.2, R96.1
V+: AMP2.P$29 (PVDD_CD), AMP2.P$30 (PVDD_CD), AMP2.P$31 (PVDD_CD), AMP2.P$36 (PVDD_AB), AMP2.P$37 (PVDD_AB), AMP2.P$38 (PVDD_AB), C120.1, C121.1, C122.1, C123.1, C124.+, C125.+; also elsewhere on the board
VMID1: C147.1, C148.1, IC4.3 (+IN), IC4.5 (+IN), IC5.3 (+IN), IC5.5 (+IN), R98.2, R99.2

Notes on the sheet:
Ch. C + D Amplifier
PVDD Bypass
Mode hardwired to 2xBTL (Stereo)
OpAmp voltage supply + bypass
Input Peripherals
